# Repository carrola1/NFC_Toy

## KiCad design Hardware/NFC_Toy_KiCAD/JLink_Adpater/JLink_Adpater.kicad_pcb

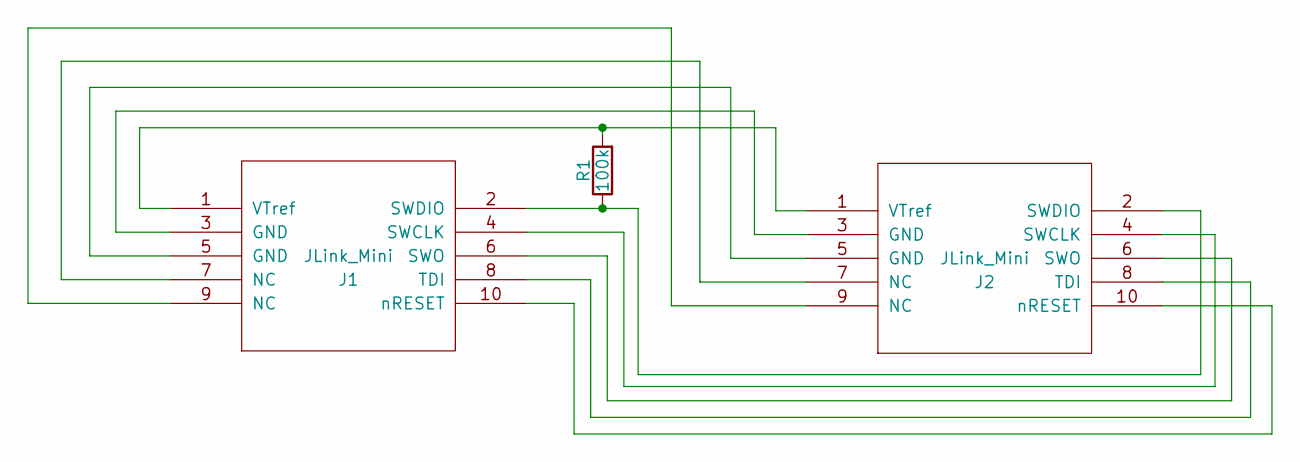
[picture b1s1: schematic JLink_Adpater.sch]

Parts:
J1: JLink_Mini; JLink_Mini_0p05_inverted
J2: JLink_Mini; J-Link_0p1in_inverted
R1: 100k; R_0603_HandSoldering

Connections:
unnamed: J1.1 (VTref), J2.1 (VTref), R1.2
unnamed: J1.2 (SWDIO), J2.2 (SWDIO), R1.1
unnamed: J1.3 (GND), J2.3 (GND)
unnamed: J1.4 (SWCLK), J2.4 (SWCLK)
unnamed: J1.5 (GND), J2.5 (GND)
unnamed: J1.6 (SWO), J2.6 (SWO)
unnamed: J1.7 (NC), J2.7 (NC)
unnamed: J1.8 (TDI), J2.8 (TDI)
unnamed: J1.9 (NC), J2.9 (NC)
unnamed: J1.10 (nRESET), J2.10 (nRESET)

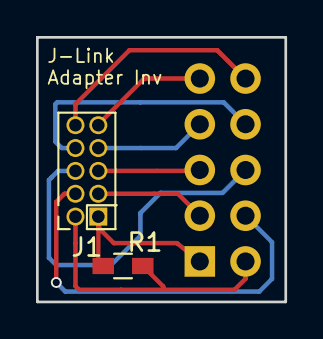
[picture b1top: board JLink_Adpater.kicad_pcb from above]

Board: 2 copper layers, 13.8 x 14.7 mm, 3 parts (1 on the bottom side), 10 nets.

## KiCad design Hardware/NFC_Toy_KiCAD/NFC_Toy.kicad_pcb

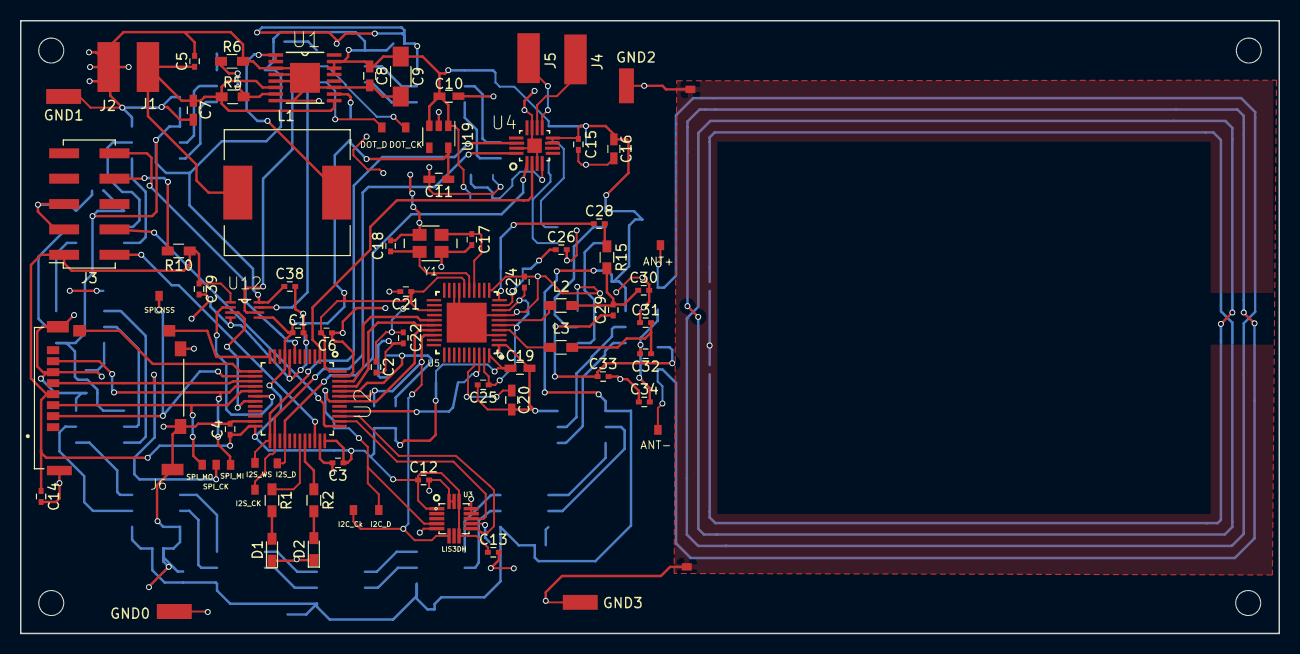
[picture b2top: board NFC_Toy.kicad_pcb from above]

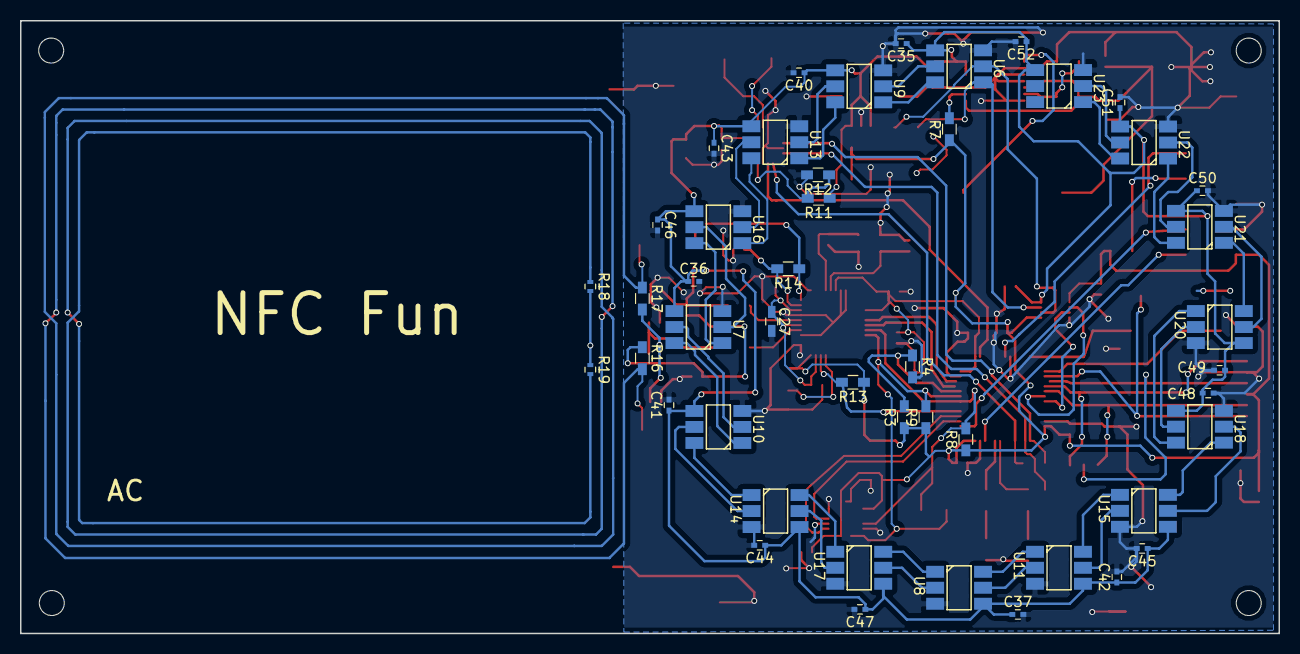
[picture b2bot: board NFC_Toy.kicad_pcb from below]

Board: 2 copper layers, 126.0 x 61.3 mm, 128 parts (46 on the bottom side), 85 nets.

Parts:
ANT+: TEST; Test_Point
ANT-: TEST; Test_Point
C1, C2, C3, C4, C5, C6, C12, C13, C14, C15, C21, C22, C24, C25, C26, C35, C36, C37, C38, C39, C40, C41, C42, C43, C44, C45, C46, C47, C48, C49, C50, C51, C52: 0.1u; C_0402
C7, C16, C19, C20, C27: 10u; C_0603_HandSoldering
C8, C11: 2.2u; C_0603_HandSoldering
C9: 220u; C_1206_HandSoldering
C10: 1u; C_0603_HandSoldering
C17, C18: 33p; C_0402
C28: 1000p; C_0402
C29, C32: 22p; C_0402
C30, C31: 220p; C_0402
C33, C34: 100p; C_0402
D1, D2: LED; LED_0603_HandSoldering
DOT_CK: TEST; Test_Point
DOT_D: TEST; Test_Point
GND0, GND1, GND2, GND3, GND4, GND4#2: TEST; Test_Point
I2C_Ck, I2C_D, I2S_CK, I2S_D, I2S_WS: TEST; Test_Point
J1, J2: Pad; Pad_SMD_Small
J3: JLink_Mini; Socket_Strip_Straight_2x05_Pitch2.54mm_SMD
J4: SPKR-; Pad_SMD_Small
J5: SPKR+; Pad_SMD_Small
J6: 503182-1852; MOLEX_503182-1852
L1: 6.8u; L_12x12mm_h4.5mm
L2, L3: 560n; L_0603_HandSoldering
MK1, MK2, MK3, MK4: Mounting_Hole; MountingHole_2.5mm
R1, R2: 121; R_0603_HandSoldering
R3, R11, R12: DNP; R_0603_HandSoldering
R4, R6, R7, R8, R9, R10, R13: 10k; R_0603_HandSoldering
R5: 30k; R_0603_HandSoldering
R14: 1k; R_0603_HandSoldering
R15: 1.6k; R_0603_HandSoldering
R16, R17: 1.5; R_0603_HandSoldering
R18, R19: 0; R_0402
SPI_CK: TEST; Test_Point
SPI_MI: TEST; Test_Point
SPI_MO: TEST; Test_Point
SPI_NSS: TEST; Test_Point
U1: TPS61032; SOP65P640X120-17N
U2: STM32L0-LQFP48; QFP50P900X900X160-48N
U3: LIS3DH; LGA16R50P5X3_300X300X100N
U4: MAX98357; QFN50P300X300X80-17N
U5: PN532; HVQFN40-6X6
U6, U7, U8, U9, U10, U11, U13, U14, U15, U16, U17, U18, U20, U21, U22, U23: APA102; APA102_hand_solder
U12: SN74LVC2T45; SOP50P310X90-8N
U19: MIC5225; SOT-23-5
Y1: Oscillator; OSCCC500X320X105N

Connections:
+3V3: C1.1, C2.1, C3.1, C4.1, C6.1, C11.1, C12.1, C13.1, C14.1, C19.1, C21.1, C22.1, C39.1, J3.1, J6.4, R3.1, R7.1, R8.1, R9.1, R10.1, R13.1, U2.1, U2.9, U2.24, U2.36, U2.48, U3.1, U3.8, U3.14, U5.16, U5.23, U5.40, U12.1, U12.5, U19.5
+5V: C8.1, C9.1, C10.1, C15.1, C16.1, C35.1, C36.1, C37.1, C38.1, C40.1, C41.1, C42.1, C43.1, C44.1, C45.1, C46.1, C47.1, C48.1, C49.1, C50.1, C51.1, C52.1, R11.1, U1.13, U1.14, U1.15, U4.7, U4.8, U6.4, U7.4, U8.4, U9.4, U10.4, U11.4, U12.8, U13.4, U14.4, U15.4, U16.4, U17.4, U18.4, U19.1, U19.3, U20.4, U21.4, U22.4, U23.4
+BATT: C5.1, C7.1, J1.1, L1.1, R5.1, U1.6, U1.9
AUDIO_SD_N: U2.2, U4.2
DotStar_CO_0: U7.2, U16.5
DotStar_CO_1: U8.2, U17.5
DotStar_CO_2: U18.5, U20.2
DotStar_Clk_3V: U2.19, U12.3
DotStar_Clk_5V: DOT_CK.1, U6.2, U12.6
DotStar_DO_0: U7.1, U16.6
DotStar_DO_1: U8.1, U17.6
DotStar_DO_2: U18.6, U20.1
DotStar_Data_3V: U2.18, U12.2
DotStar_Data_5V: DOT_D.1, U6.1, U12.7
GND: C1.2, C2.2, C3.2, C4.2, C5.2, C6.2, C7.2, C8.2, C9.2, C10.2, C11.2, C12.2, C13.2, C14.2, C15.2, C16.2, C17.2, C18.2, C19.2, C20.2, C21.2, C22.2, C24.2, C25.2, C26.2, C27.2, C30.2, C31.1, C33.2, C34.1, C35.2, C36.2, C37.2, C38.2, C39.2, C40.2, C41.2, C42.2, C43.2, C44.2, C45.2, C46.2, C47.2, C48.2, C49.2, C50.2, C51.2, C52.2, D1.1, D2.1, GND0.1, GND1.1, GND2.1, GND3.1, GND4.1, GND4#2.1, J2.1, J3.3, J3.5, J6.6, J6.P1, J6.P2, J6.P3, J6.P4, J6.P5, R4.2, R6.2, R12.2, R18.2, R19.1, U1.3, U1.4, U1.5, U1.8, U1.11, U1.17, U2.8, U2.23, U2.35, U2.47, U3.5, U3.10, U3.12, U3.13, U3.15, U3.16, U4.3, U4.11, U4.15, U4.17, U5.1, U5.3, U5.7, U5.11, U5.17, U5.18, U5.TP, U6.3, U7.3, U8.3, U9.3, U10.3, U11.3, U12.4, U13.3, U14.3, U15.3, U16.3, U17.3, U18.3, U19.2, U20.3, U21.3, U22.3, U23.3, Y1.2, Y1.4
I2C_SCL: I2C_D.1, R8.2, U2.42, U3.4, U5.27
I2C_SDA: I2C_Ck.1, R9.2, U2.43, U3.6, U5.28
I2S_CK: I2S_CK.1, U2.26, U4.16
I2S_SD: I2S_D.1, U2.28, U4.1
I2S_WS: I2S_WS.1, U2.25, U4.14
NFC_IRQ: U2.46, U5.25
NFC_RST_N: U2.45, U5.26
NFC_RST_PDN_N: R13.2, U2.40, U5.38
unnamed: C17.1, U5.14, Y1.1
unnamed: C18.1, U5.15, Y1.3
unnamed: C20.1, U5.37
unnamed: C26.1, R14.2, U5.9
unnamed: C28.1, R14.1, U5.10
unnamed: C28.2, R15.1
unnamed: C29.1, C33.1, R16.1
unnamed: C29.2, C30.1, L2.2, R15.2
unnamed: C31.2, C32.1, L3.2
unnamed: C32.2, C34.2, R17.2
unnamed: D1.2, R1.2
unnamed: D2.2, R2.2
unnamed: J3.8, R10.2
unnamed: J4.1, U4.10
unnamed: J5.1, U4.9
unnamed: L1.2, U1.1, U1.2
unnamed: L2.1, U5.6
unnamed: L3.1, U5.4
unnamed: R1.1, U2.31
unnamed: R2.1, U2.32
unnamed: R3.2, R4.1, U2.44
unnamed: R5.2, R6.1, U1.7
unnamed: R7.2, U1.10
unnamed: R11.2, R12.1, U4.4
unnamed: ANT-.1, R16.2, R18.1
unnamed: ANT+.1, R17.1, R19.2
unnamed: U6.5, U9.2
unnamed: U6.6, U9.1
unnamed: U7.6, U10.1
unnamed: U7.5, U10.2
unnamed: U10.5, U14.2
unnamed: U10.6, U14.1
unnamed: U8.6, U11.1
unnamed: U8.5, U11.2
unnamed: U11.5, U15.2
unnamed: U11.6, U15.1
unnamed: U9.6, U13.1
unnamed: U9.5, U13.2
unnamed: U13.5, U16.2
unnamed: U13.6, U16.1
unnamed: U14.5, U17.2
unnamed: U14.6, U17.1
unnamed: U15.5, U18.2
unnamed: U15.6, U18.1
unnamed: U20.5, U21.2
unnamed: U20.6, U21.1
unnamed: U21.5, U22.2
unnamed: U21.6, U22.1
unnamed: U22.5, U23.2
unnamed: U22.6, U23.1
SD_DETECT: J6.DT, U2.12
SD_SW: J6.SW, U2.13
SPI_MISO: J6.7, SPI_MI.1, U2.16
SPI_MOSI: J6.3, SPI_MO.1, U2.17
SPI_NSS: J6.2, SPI_NSS.1, U2.14
SPI_SCK: J6.5, SPI_CK.1, U2.15
SWCLK: J3.4, U2.37
SWDIO: J3.2, U2.34
VCC: C24.1, C25.1, C27.1, U5.5, U5.8, U5.39
XL_INT1: U2.38, U3.11
XL_INT2: U2.39, U3.9
nRST: J3.10, U2.7

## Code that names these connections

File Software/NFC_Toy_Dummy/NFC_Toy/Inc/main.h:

/* USER CODE BEGIN Header */
/**
  ******************************************************************************
  * @file           : main.h
  * @brief          : Header for main.c file.
  *                   This file contains the common defines of the application.
  ******************************************************************************
  * @attention
  *
  * <h2><center>&copy; Copyright (c) 2019 STMicroelectronics.
  * All rights reserved.</center></h2>
  *
  * This software component is licensed by ST under Ultimate Liberty license
  * SLA0044, the "License"; You may not use this file except in compliance with
  * the License. You may obtain a copy of the License at:
  *                             www.st.com/SLA0044
  *
  ******************************************************************************
  */
/* USER CODE END Header */

/* Define to prevent recursive inclusion -------------------------------------*/
#ifndef __MAIN_H
#define __MAIN_H

#ifdef __cplusplus
extern "C" {
#endif

/* Includes ------------------------------------------------------------------*/
#include "stm32l0xx_hal.h"

/* Private includes ----------------------------------------------------------*/
/* USER CODE BEGIN Includes */

/* USER CODE END Includes */

/* Exported types ------------------------------------------------------------*/
/* USER CODE BEGIN ET */

/* USER CODE END ET */

/* Exported constants --------------------------------------------------------*/
/* USER CODE BEGIN EC */

/* USER CODE END EC */

/* Exported macro ------------------------------------------------------------*/
/* USER CODE BEGIN EM */

/* USER CODE END EM */

/* Exported functions prototypes ---------------------------------------------*/
void Error_Handler(void);

/* USER CODE BEGIN EFP */

/* USER CODE END EFP */

/* Private defines -----------------------------------------------------------*/
#define AUDIO_SD_N_Pin GPIO_PIN_13
#define AUDIO_SD_N_GPIO_Port GPIOC
#define SD_DETECT_Pin GPIO_PIN_2
#define SD_DETECT_GPIO_Port GPIOA
#define SD_SW_Pin GPIO_PIN_3
#define SD_SW_GPIO_Port GPIOA
#define SD_CS_Pin GPIO_PIN_4
#define SD_CS_GPIO_Port GPIOA
#define DOT_STAR_DATA_Pin GPIO_PIN_0
#define DOT_STAR_DATA_GPIO_Port GPIOB
#define DOT_STAR_CLK_Pin GPIO_PIN_1
#define DOT_STAR_CLK_GPIO_Port GPIOB
#define LED_1_Pin GPIO_PIN_10
#define LED_1_GPIO_Port GPIOA
#define LED_2_Pin GPIO_PIN_11
#define LED_2_GPIO_Port GPIOA
#define XL_INT1_Pin GPIO_PIN_15
#define XL_INT1_GPIO_Port GPIOA
#define XL_INT1_EXTI_IRQn EXTI4_15_IRQn
#define XL_INT2_Pin GPIO_PIN_3
#define XL_INT2_GPIO_Port GPIOB
#define NFC_RST_PDN_N_Pin GPIO_PIN_4
#define NFC_RST_PDN_N_GPIO_Port GPIOB
#define NFC_RST_N_Pin GPIO_PIN_8
#define NFC_RST_N_GPIO_Port GPIOB
#define NFC_IRQ_Pin GPIO_PIN_9
#define NFC_IRQ_GPIO_Port GPIOB
/* USER CODE BEGIN Private defines */

/* USER CODE END Private defines */

#ifdef __cplusplus
}
#endif

#endif /* __MAIN_H */

/************************ (C) COPYRIGHT STMicroelectronics *****END OF FILE****/

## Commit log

2018-04-12 :tada: Added .gitattributes & .gitignore files
2018-04-13 Ready to start layout
2018-04-17 Layout started
2018-04-23 Component placement complete.
2018-04-25 Layout 75% complete
2018-04-27 First pass layout complete
2018-04-30 Preliminary layout complete
2018-05-02 Submitted to PCBWay for build
2018-05-17 Added J-Link adapter and 1st cut of software
2018-05-30 Added inverted JLink adapter. First working code.
2018-06-04 Dotstar, accelerometer, audio working
2018-06-15 SD SPI interface working but getting FR_NOT_READY.
2018-06-18 Able to read .wav from SD Card.
2018-06-29 Added PN532 library. Not sure it's working yet.
    Audio is playing correctly from buffer but there are long delays between each byte read from SD card. Causes long delays between writing out buffers to audio amp.
2018-07-12 Audio appears to be working but only getting static
    Finally got I2S and SD card read timing working. Correct audio samples appear to be going out I2S and no I2S pauses between SD card reads.
2018-07-19 Able to recognize unique tag IDs.
2018-07-23 Now going to sleep after timeout and waking up with motion.
2019-02-22 Added enclosure .stl
2019-04-08 v1.0
    First implementation given to the kids.
2019-06-26 Added RNG and "Try Again"
2020-01-07 Fixed audio distortion and migrated to STM32CUBEIDE
    Secret was to change GPIO speed of I2S signals from LOW to HIGH.
2020-01-08 LEDs now reflect color to be found.
2020-03-26 Mostly working scheduler implemented
2020-03-26 Changed to single state machine
    Task scheduler was interesting, but didn't make sense for this application. This single state machine is super simple and works great.
